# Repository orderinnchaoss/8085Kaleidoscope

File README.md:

# 8085 Kaleidoscope Under the guidance of Professor D.V.Gadre
This contains files 8085 

Includes

1)Schematics and Board Files

2)Main Code(Text,Hex,Bin)

3)Report

4)Program Flowchart

5)Bill of Material

Can be reproduced with permission, by the contacts under

Made by 
 Priyanshu Pandey 130/EC/15 - 95608-59659 - priyanshupandey7997@gmail.com / priyanshup.ec@nsit.net.in
 Nishant Arora 110/EC/15 - 78387-67240 - arora.nishant97@gmail.com

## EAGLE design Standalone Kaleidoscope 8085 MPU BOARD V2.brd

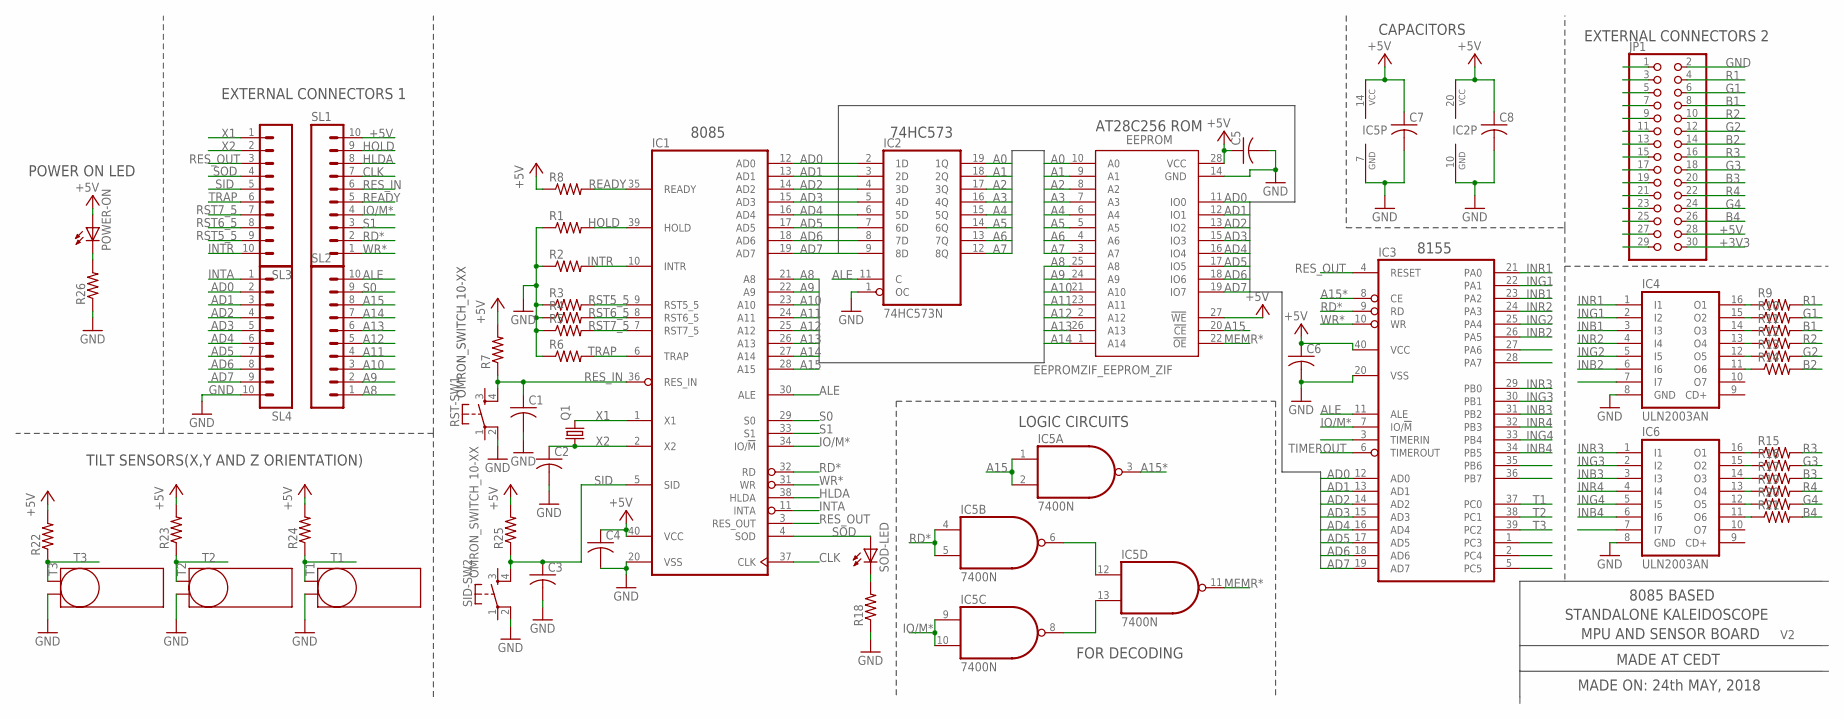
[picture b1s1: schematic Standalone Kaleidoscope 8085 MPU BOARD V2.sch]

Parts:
C1, C2, C3, C4, C5, C6: C-USC0805K; C0805K
C7, C8: C-USC0805; C0805
EEPROM: EEPROMZIF_EEPROM_ZIF; EEPROMZIF_DIL28-6-ZIF_SOCKET
IC1: 8085; DIL40
IC2: 74HC573N; DIL20
IC3: 8155; DIL40
IC4, IC6: ULN2003AN; DIL16
IC5: 7400N; DIL14
JP1: PINHD-2X15; 2X15
POWER-ON: LEDCHIP-LED0805; CHIP-LED0805
Q1: CEDT_JANUARY_2015_V5_A_CRYSTALHC49US; CEDT_JANUARY_2015_V5_A_HC49US
R1, R2, R3, R4, R5, R6, R7, R8, R9, R10, R11, R12, R13, R14, R15, R16, R17, R18, R19, R20, R21, R22, R23, R24, R25, R26: R-US_R0805; R0805
RST-SW1: OMRON_SWITCH_10-XX; B3F-10XX
SID-SW2: OMRON_SWITCH_10-XX; B3F-10XX
SL1, SL2, SL3, SL4: CON-AMP-QUICK_M10; CON-AMP-QUICK_10P
SOD-LED: LEDCHIP-LED0805; CHIP-LED0805
T1, T2, T3: TILTSENSORE2.5-7; TILTSENSOR

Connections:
+3V3: JP1.29, JP1.30
+5V: C4.1, C5.1, C6.1, C7.1, C8.1, EEPROM.27 (!WE), EEPROM.28 (VCC), IC1.40 (VCC), IC2.20 (VCC), IC3.40 (VCC), IC5.14 (VCC), JP1.27, JP1.28, POWER-ON.A, R7.2, R8.1, R22.2, R23.2, R24.2, R25.2, SL1.10
A0: EEPROM.10 (A0), IC2.19 (1Q)
A1: EEPROM.9 (A1), IC2.18 (2Q)
A2: EEPROM.8 (A2), IC2.17 (3Q)
A3: EEPROM.7 (A3), IC2.16 (4Q)
A4: EEPROM.6 (A4), IC2.15 (5Q)
A5: EEPROM.5 (A5), IC2.14 (6Q)
A6: EEPROM.4 (A6), IC2.13 (7Q)
A7: EEPROM.3 (A7), IC2.12 (8Q)
A8: EEPROM.25 (A8), IC1.21 (A8), SL2.1
A9: EEPROM.24 (A9), IC1.22 (A9), SL2.2
A10: EEPROM.21 (A10), IC1.23 (A10), SL2.3
A11: EEPROM.23 (A11), IC1.24 (A11), SL2.4
A12: EEPROM.2 (A12), IC1.25 (A12), SL2.5
A13: EEPROM.26 (A13), IC1.26 (A13), SL2.6
A14: EEPROM.1 (A14), IC1.27 (A14), SL2.7
A15: EEPROM.20 (!CE), IC1.28 (A15), IC5.1 (I0), IC5.2 (I1), SL2.8
A15*: IC3.8 (CE), IC5.3 (O)
AD0: EEPROM.11 (IO0), IC1.12 (AD0), IC2.2 (1D), IC3.12 (AD0), SL4.2
AD1: EEPROM.12 (IO1), IC1.13 (AD1), IC2.3 (2D), IC3.13 (AD1), SL4.3
AD2: EEPROM.13 (IO2), IC1.14 (AD2), IC2.4 (3D), IC3.14 (AD2), SL4.4
AD3: EEPROM.15 (IO3), IC1.15 (AD3), IC2.5 (4D), IC3.15 (AD3), SL4.5
AD4: EEPROM.16 (IO4), IC1.16 (AD4), IC2.6 (5D), IC3.16 (AD4), SL4.6
AD5: EEPROM.17 (IO5), IC1.17 (AD5), IC2.7 (6D), IC3.17 (AD5), SL4.7
AD6: EEPROM.18 (IO6), IC1.18 (AD6), IC2.8 (7D), IC3.18 (AD6), SL4.8
AD7: EEPROM.19 (IO7), IC1.19 (AD7), IC2.9 (8D), IC3.19 (AD7), SL4.9
ALE: IC1.30 (ALE), IC2.11 (C), IC3.11 (ALE), SL2.10
B1: JP1.7, JP1.8, R11.2
B2: JP1.13, JP1.14, R14.2
B3: JP1.19, JP1.20, R17.2
B4: JP1.25, JP1.26, R21.2
CLK: IC1.37 (CLK), SL1.7
G1: JP1.5, JP1.6, R10.2
G2: JP1.11, JP1.12, R13.2
G3: JP1.17, JP1.18, R16.2
G4: JP1.23, JP1.24, R20.2
GND: C1.2, C2.2, C3.2, C4.2, C5.2, C6.2, C7.2, C8.2, EEPROM.14 (GND), IC1.20 (VSS), IC2.1 (OC), IC2.10 (GND), IC3.20 (VSS), IC4.8 (GND), IC5.7 (GND), IC6.8 (GND), JP1.1, JP1.2, R1.1, R2.1, R3.1, R4.1, R5.1, R6.1, R18.1, R26.1, RST-SW1.2 (P1), SID-SW2.2 (P1), SL4.10, T1.-, T2.-, T3.-
HLDA: IC1.38 (HLDA), SL1.8
HOLD: IC1.39 (HOLD), R1.2, SL1.9
INB1: IC3.23 (PA2), IC4.3 (I3)
INB2: IC3.26 (PA5), IC4.6 (I6)
INB3: IC3.31 (PB2), IC6.3 (I3)
INB4: IC3.34 (PB5), IC6.6 (I6)
ING1: IC3.22 (PA1), IC4.2 (I2)
ING2: IC3.25 (PA4), IC4.5 (I5)
ING3: IC3.30 (PB1), IC6.2 (I2)
ING4: IC3.33 (PB4), IC6.5 (I5)
INR1: IC3.21 (PA0), IC4.1 (I1)
INR2: IC3.24 (PA3), IC4.4 (I4)
INR3: IC3.29 (PB0), IC6.1 (I1)
INR4: IC3.32 (PB3), IC6.4 (I4)
INTA: IC1.11 (INTA), SL4.1
INTR: IC1.10 (INTR), R2.2, SL3.10
IO/M*: IC1.34 (IO/!M), IC3.7 (IO/!M), IC5.9 (I0), IC5.10 (I1), SL1.4
MEMR*: EEPROM.22 (!OE), IC5.11 (O)
unnamed: POWER-ON.C, R26.2
unnamed: IC4.16 (O1), R9.1
unnamed: IC4.15 (O2), R10.1
unnamed: IC4.14 (O3), R11.1
unnamed: IC5.6 (O), IC5.12 (I0)
unnamed: IC5.8 (O), IC5.13 (I1)
unnamed: IC4.13 (O4), R12.1
unnamed: IC4.12 (O5), R13.1
unnamed: IC4.11 (O6), R14.1
unnamed: IC6.11 (O6), R21.1
unnamed: IC6.12 (O5), R20.1
unnamed: IC6.13 (O4), R19.1
unnamed: IC6.14 (O3), R17.1
unnamed: IC6.15 (O2), R16.1
unnamed: R18.2, SOD-LED.C
unnamed: IC6.16 (O1), R15.1
R1: JP1.3, JP1.4, R9.2
R2: JP1.9, JP1.10, R12.2
R3: JP1.15, JP1.16, R15.2
R4: JP1.21, JP1.22, R19.2
RD*: IC1.32 (RD), IC3.9 (RD), IC5.4 (I0), IC5.5 (I1), SL1.2
READY: IC1.35 (READY), R8.2, SL1.5
RES_IN: C1.1, IC1.36 (RES_IN), R7.1, RST-SW1.4 (S1), SL1.6
RES_OUT: IC1.3 (RES_OUT), IC3.4 (RESET), SL3.3
RST5_5: IC1.9 (RST5_5), R3.2, SL3.9
RST6_5: IC1.8 (RST6_5), R4.2, SL3.8
RST7_5: IC1.7 (RST7_5), R5.2, SL3.7
S0: IC1.29 (S0), SL2.9
S1: IC1.33 (S1), SL1.3
SID: C3.1, IC1.5 (SID), R25.1, SID-SW2.4 (S1), SL3.5
SOD: IC1.4 (SOD), SL3.4, SOD-LED.A
T1: IC3.37 (PC0), R24.1, T1.+
T2: IC3.38 (PC1), R23.1, T2.+
T3: IC3.39 (PC2), R22.1, T3.+
TIMEROUT: IC3.6 (TIMEROUT)
TRAP: IC1.6 (TRAP), R6.2, SL3.6
WR*: IC1.31 (WR), IC3.10 (WR), SL1.1
X1: IC1.1 (X1), Q1.2, SL3.1
X2: C2.1, IC1.2 (X2), Q1.1, SL3.2

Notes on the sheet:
TILT SENSORS(X,Y AND Z ORIENTATION)
8085
74HC573
AT28C256 ROM
CAPACITORS
8155
EXTERNAL CONNECTORS 2
EXTERNAL CONNECTORS 1
LOGIC CIRCUITS
POWER ON LED
8085 BASED
STANDALONE KALEIDOSCOPE
MADE AT CEDT
MPU AND SENSOR BOARD
MADE ON: 24th MAY, 2018
FOR DECODING

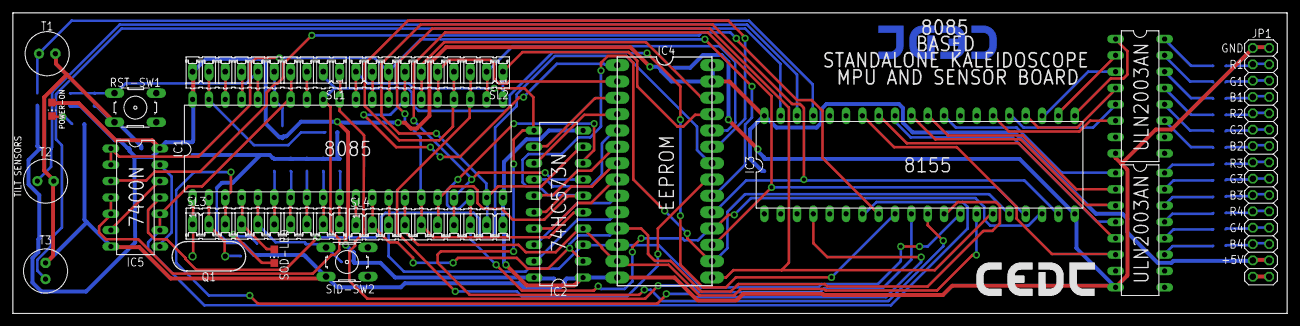
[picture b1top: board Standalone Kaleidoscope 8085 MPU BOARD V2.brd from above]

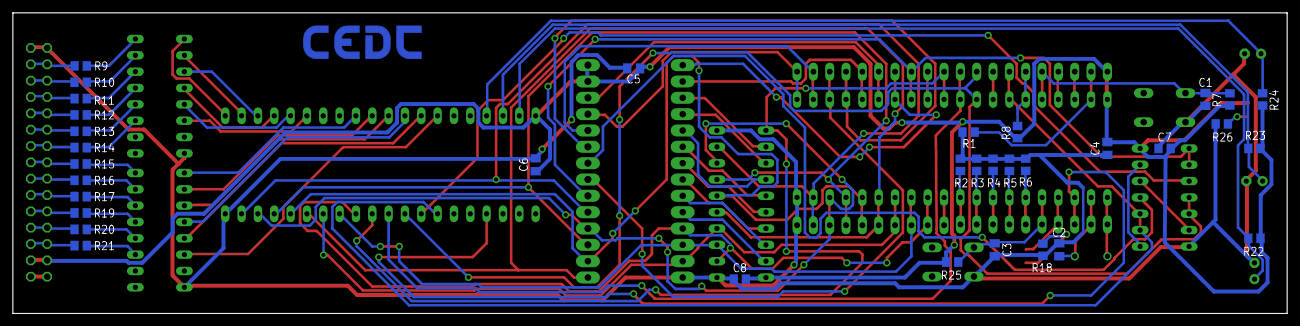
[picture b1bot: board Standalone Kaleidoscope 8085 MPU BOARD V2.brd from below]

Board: 2 copper layers, 198.1 x 46.7 mm, 56 parts (34 on the bottom side), 94 nets.

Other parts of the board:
U$1: LOGO-CEDT-BOT-18MM
U$4: LOGO-CEDT-SILK-18MM

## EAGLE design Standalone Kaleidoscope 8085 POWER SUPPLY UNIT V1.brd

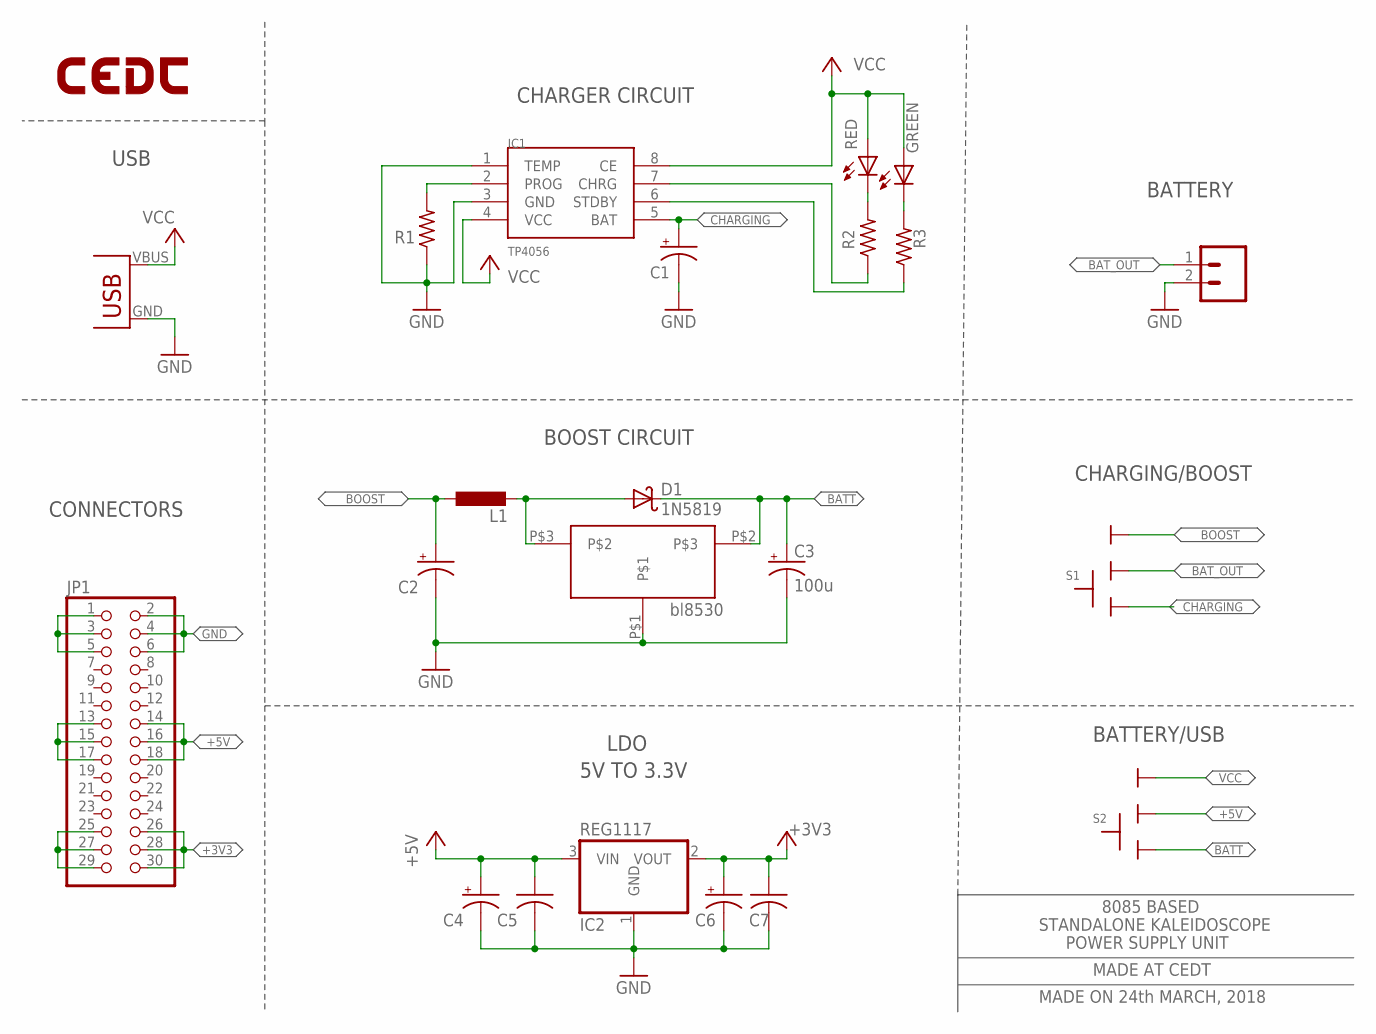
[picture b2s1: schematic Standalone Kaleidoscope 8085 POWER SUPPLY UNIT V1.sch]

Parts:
BATTERY: M02; 02P
BL8530: BL8530_5V
C1, C2, C4, C6: 10u; C/6032-28R
C3: 100u; C/6032-28R
C5, C7: 0.1u; C0805
D1: 1N5819; DO41-10
GREEN: LED3MM
IC1: TP4056; SOP-8
IC2: REG1117; SOT223
JP1: PINHD-2X15; 2X15
L1: 47uH; L4532P
LOGO1: LOGO-CEDTBOT-18MM; LOGO-CEDT-BOT-18MM
R1: RESISTOR0805; R0805
R2, R3: 470; R0805
RED: LED3MM
S1, S2: SLIDESWITCH-BIG; BIGSWITCH
U$1: USB(POWER)

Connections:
+3V3: C6.+, C7.1, IC2.2 (VOUT), JP1.25, JP1.26, JP1.27, JP1.28, JP1.29, JP1.30
+5V: C4.+, C5.1, IC2.3 (VIN), JP1.13, JP1.14, JP1.15, JP1.16, JP1.17, JP1.18, S2.2
BATT: BL8530.P$2, C3.+, D1.C, S2.1
BAT_OUT: BATTERY.1, S1.2
BOOST: C2.+, L1.1, S1.3
CHARGING: C1.+, IC1.5 (BAT), S1.1
GND: BATTERY.2, BL8530.P$1, C1.-, C2.-, C3.-, C4.-, C5.2, C6.-, C7.2, IC1.1 (TEMP), IC1.3 (GND), IC2.1 (GND), JP1.1, JP1.2, JP1.3, JP1.4, JP1.5, JP1.6, R1.1, U$1.GND
unnamed: IC1.2 (PROG), R1.2
unnamed: R2.2, RED.K (C)
unnamed: IC1.6 (STDBY), R3.1
unnamed: IC1.7 (CHRG), R2.1
unnamed: BL8530.P$3, D1.A, L1.2
unnamed: GREEN.K (C), R3.2
VCC: GREEN.A, IC1.4 (VCC), IC1.8 (CE), RED.A, S2.3, U$1.VBUS (VCC)

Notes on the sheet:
CHARGER CIRCUIT
BOOST CIRCUIT
LDO
bl8530
CONNECTORS
CHARGING/BOOST
USB
5V TO 3.3V
BATTERY/USB
8085 BASED
STANDALONE KALEIDOSCOPE
POWER SUPPLY UNIT
MADE AT CEDT
MADE ON 24th MARCH, 2018

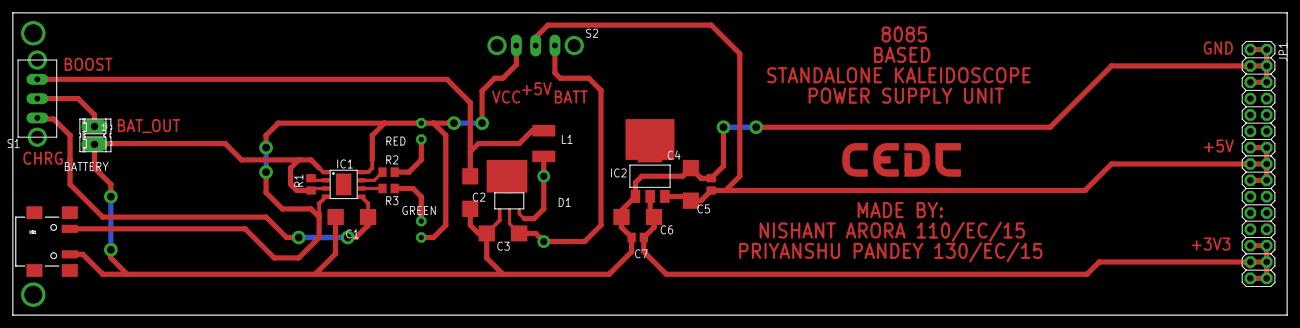
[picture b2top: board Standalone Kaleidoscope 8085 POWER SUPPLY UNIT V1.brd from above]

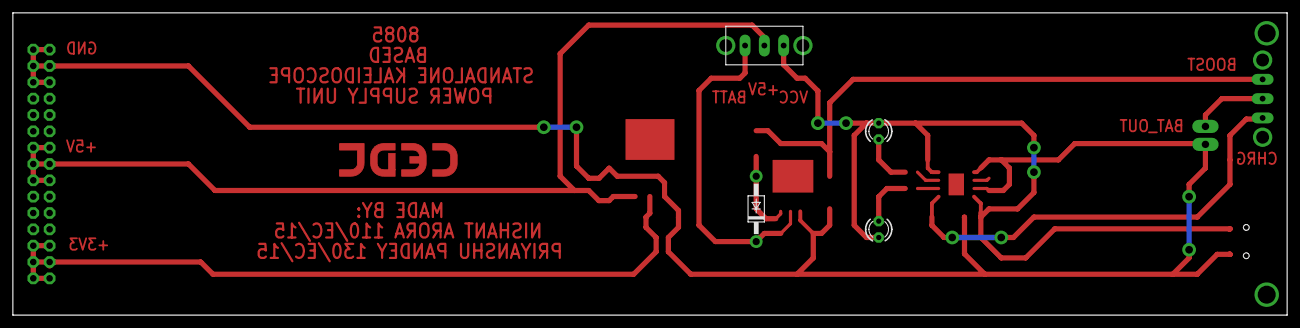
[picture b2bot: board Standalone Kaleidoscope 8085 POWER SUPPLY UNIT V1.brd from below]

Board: 2 copper layers, 198.1 x 47.0 mm, 23 parts (5 on the bottom side), 14 nets.

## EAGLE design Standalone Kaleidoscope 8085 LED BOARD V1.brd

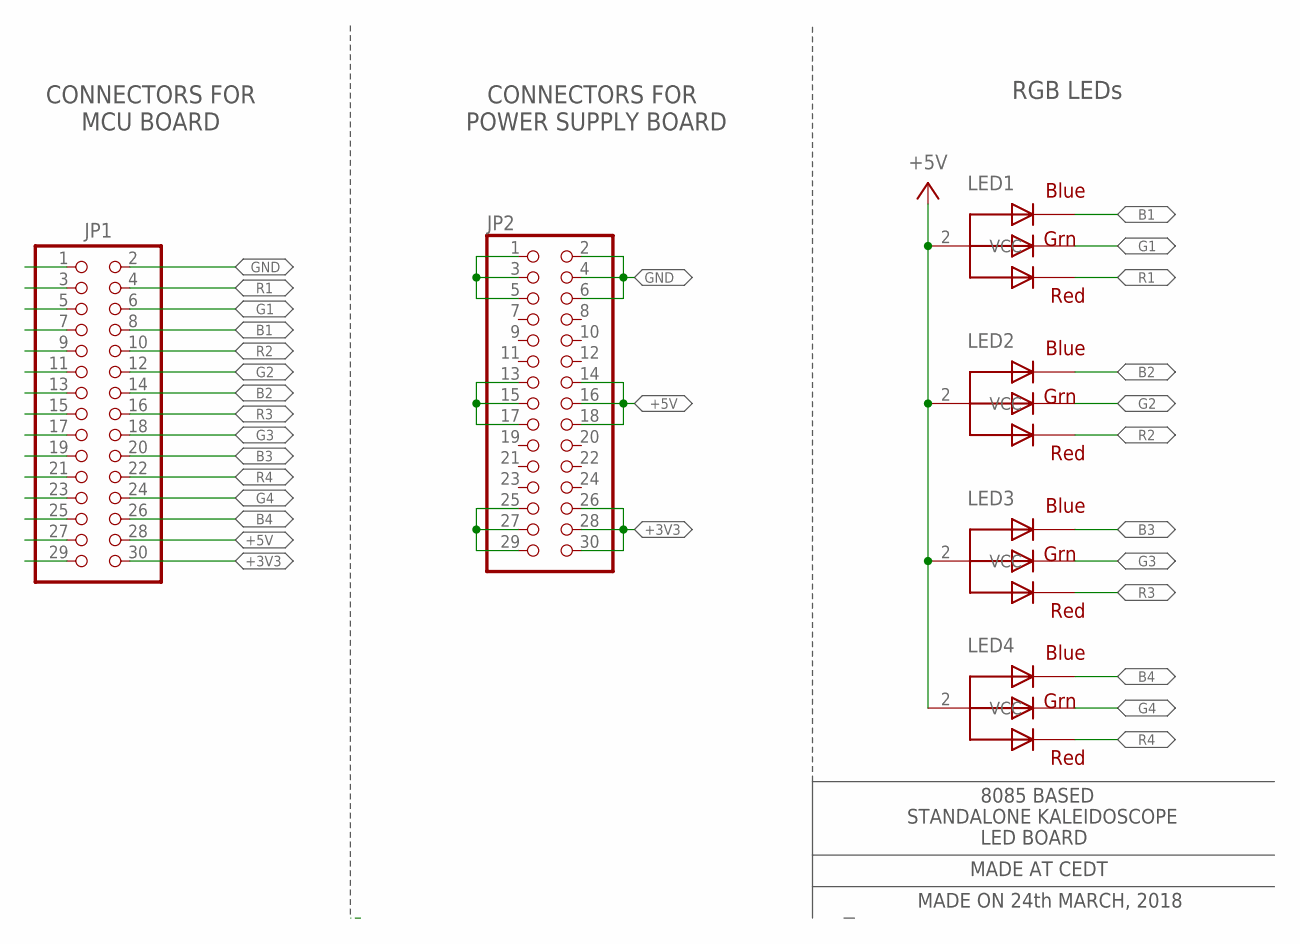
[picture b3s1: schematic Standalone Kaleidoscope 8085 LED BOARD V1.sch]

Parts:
JP1, JP2: PINHD-2X15; 2X15
LED1, LED2, LED3, LED4: RGBLED_CA; LED5MMRGB

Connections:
+3V3: JP1.29, JP1.30, JP2.25, JP2.26, JP2.27, JP2.28, JP2.29, JP2.30
+5V: JP1.27, JP1.28, JP2.13, JP2.14, JP2.15, JP2.16, JP2.17, JP2.18, LED1.2 (VCC), LED2.2 (VCC), LED3.2 (VCC), LED4.2 (VCC)
B1: JP1.7, JP1.8, LED1.4 (BLUE)
B2: JP1.13, JP1.14, LED2.4 (BLUE)
B3: JP1.19, JP1.20, LED3.4 (BLUE)
B4: JP1.25, JP1.26, LED4.4 (BLUE)
G1: JP1.5, JP1.6, LED1.3 (GREEN)
G2: JP1.11, JP1.12, LED2.3 (GREEN)
G3: JP1.17, JP1.18, LED3.3 (GREEN)
G4: JP1.23, JP1.24, LED4.3 (GREEN)
GND: JP1.1, JP1.2, JP2.1, JP2.2, JP2.3, JP2.4, JP2.5, JP2.6
R1: JP1.3, JP1.4, LED1.1 (RED)
R2: JP1.9, JP1.10, LED2.1 (RED)
R3: JP1.15, JP1.16, LED3.1 (RED)
R4: JP1.21, JP1.22, LED4.1 (RED)

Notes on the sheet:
CONNECTORS FOR MCU BOARD
CONNECTORS FOR POWER SUPPLY BOARD
RGB LEDs
8085 BASED
STANDALONE KALEIDOSCOPE
LED BOARD
MADE AT CEDT
MADE ON 24th MARCH, 2018

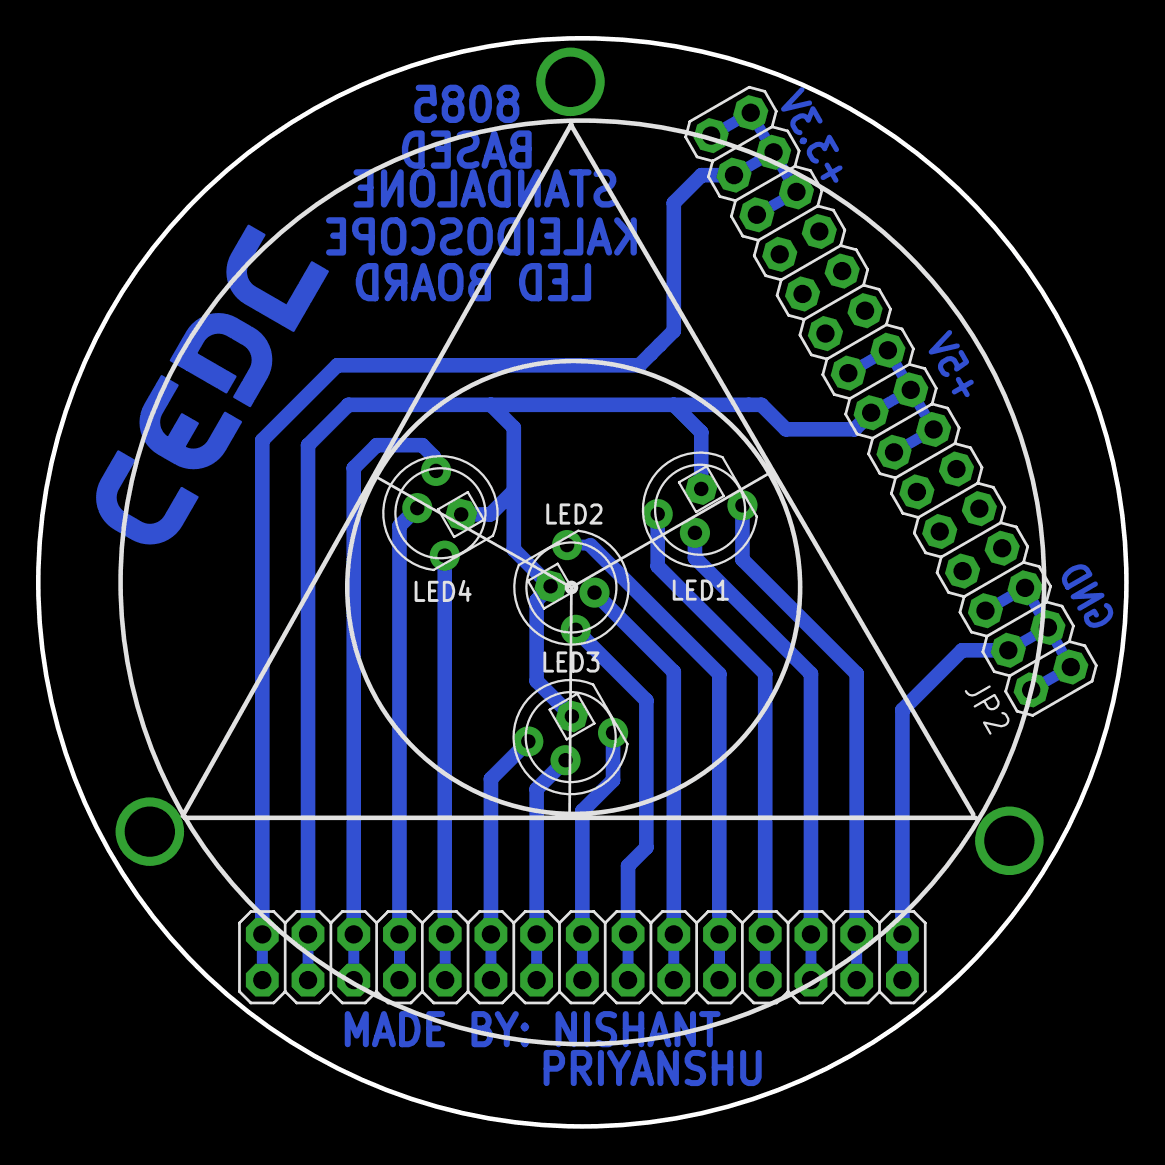
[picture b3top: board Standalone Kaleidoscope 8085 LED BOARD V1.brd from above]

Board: 2 copper layers, 60.5 x 60.5 mm, 7 parts (0 on the bottom side), 15 nets.

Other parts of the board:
U$1: LOGO-CEDT-BOT-18MM

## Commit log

2018-05-22 Update README.md
    Contains the code
2018-05-22 Maincode
